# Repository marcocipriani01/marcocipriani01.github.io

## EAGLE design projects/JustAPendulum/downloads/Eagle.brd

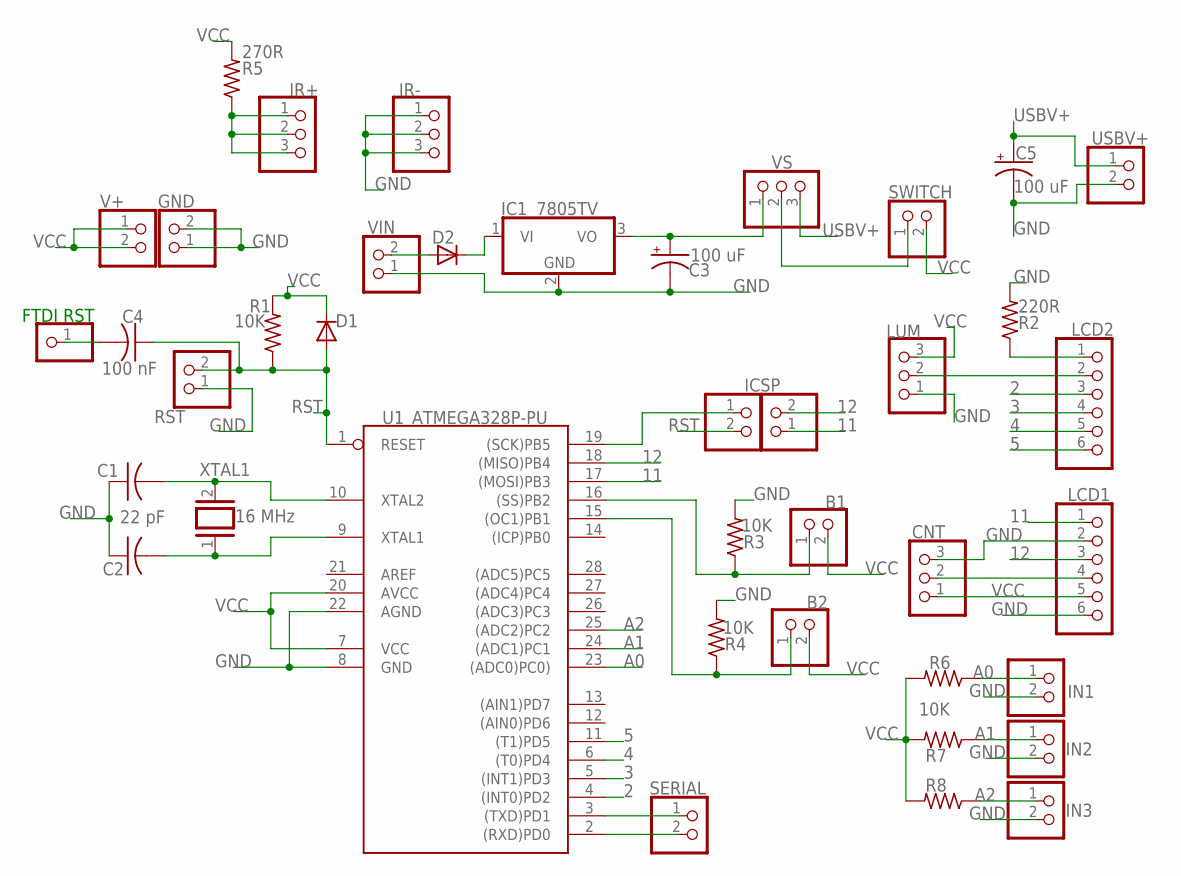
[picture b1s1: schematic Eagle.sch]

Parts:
B1, B2: PINHD-1X2; 1X02
C1, C2: 22 pF; C025-025X050
C3: 100 uF; E5-6
C4: 100 nF; C102-043X133
C5: 100 uF; B45181A
CNT: PINHD-1X3; 1X03
D1, D2: 1N4148DO35-7; DO35-7
FTDI_RST: PINHD-1X1; 1X01
GND: PINHD-1X2; 1X02
IC1: 7805TV; TO220V
ICSP, ICSP2: PINHD-1X2; 1X02
IN1, IN2, IN3: PINHD-1X2; 1X02
IR+: PINHD-1X3; 1X03
IR-: PINHD-1X3; 1X03
LCD1, LCD2: PINHD-1X6; 1X06
LUM: PINHD-1X3; 1X03
R1, R3, R4, R6, R7, R8: 10K; 0204/5
R2: 220R; 0204/5
R5: 270R; 0207/10
RST: PINHD-1X2; 1X02
SERIAL: PINHD-1X2; 1X02
SWITCH: PINHD-1X2; 1X02
U1: ATMEGA328P-PU; DIL28-3
USBV+: PINHD-1X2; 1X02
V+: PINHD-1X2; 1X02
VIN: PINHD-1X2; 1X02
VS: PINHD-1X3; 1X03
XTAL1: 16 MHz; QS

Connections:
2: LCD2.3, U1.4 ((INT0)PD2)
3: LCD2.4, U1.5 ((INT1)PD3)
4: LCD2.5, U1.6 ((T0)PD4)
5: LCD2.6, U1.11 ((T1)PD5)
10: B1.1, R3.1, U1.16 ((SS)PB2)
11: ICSP2.1, LCD1.1, U1.17 ((MOSI)PB3)
12: ICSP2.2, LCD1.3, U1.18 ((MISO)PB4)
A0: IN1.1, R6.1, U1.23 ((ADC0)PC0))
A1: IN2.1, R7.1, U1.24 ((ADC1)PC1)
A2: IN3.1, R8.1, U1.25 ((ADC2)PC2)
GND: C1.1, C2.1, C3.-, C5.-, CNT.3, GND.1, GND.2, IC1.2 (GND), IN1.2, IN2.2, IN3.2, IR-.1, IR-.2, IR-.3, LCD1.2, LCD1.6, LUM.1, R2.2, R3.2, R4.2, RST.1, U1.8 (GND), U1.22 (AGND), USBV+.2, VIN.1
unnamed: C3.+, IC1.3 (VO), VS.1
unnamed: C1.2, U1.10 (XTAL2), XTAL1.2
unnamed: C2.2, U1.9 (XTAL1), XTAL1.1
unnamed: D2.A, VIN.2
unnamed: D2.C, IC1.1 (VI)
unnamed: C4.2, FTDI_RST.1
unnamed: ICSP.1, U1.19 ((SCK)PB5)
unnamed: B2.1, R4.1, U1.15 ((OC1)PB1)
unnamed: SWITCH.1, VS.2
unnamed: LCD2.1, R2.1
unnamed: CNT.2, LCD1.4
unnamed: LCD2.2, LUM.2
unnamed: IR+.1, IR+.2, IR+.3, R5.1
RST: C4.1, D1.A, ICSP.2, R1.1, RST.2, U1.1 (RESET)
RX: SERIAL.2, U1.2 ((RXD)PD0)
TX: SERIAL.1, U1.3 ((TXD)PD1)
USBV+: C5.+, USBV+.1, VS.3
VCC: B1.2, B2.2, CNT.1, D1.C, LCD1.5, LUM.3, R1.2, R5.2, R6.2, R7.2, R8.2, SWITCH.2, U1.7 (VCC), U1.20 (AVCC), V+.1, V+.2

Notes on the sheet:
FTDI RST

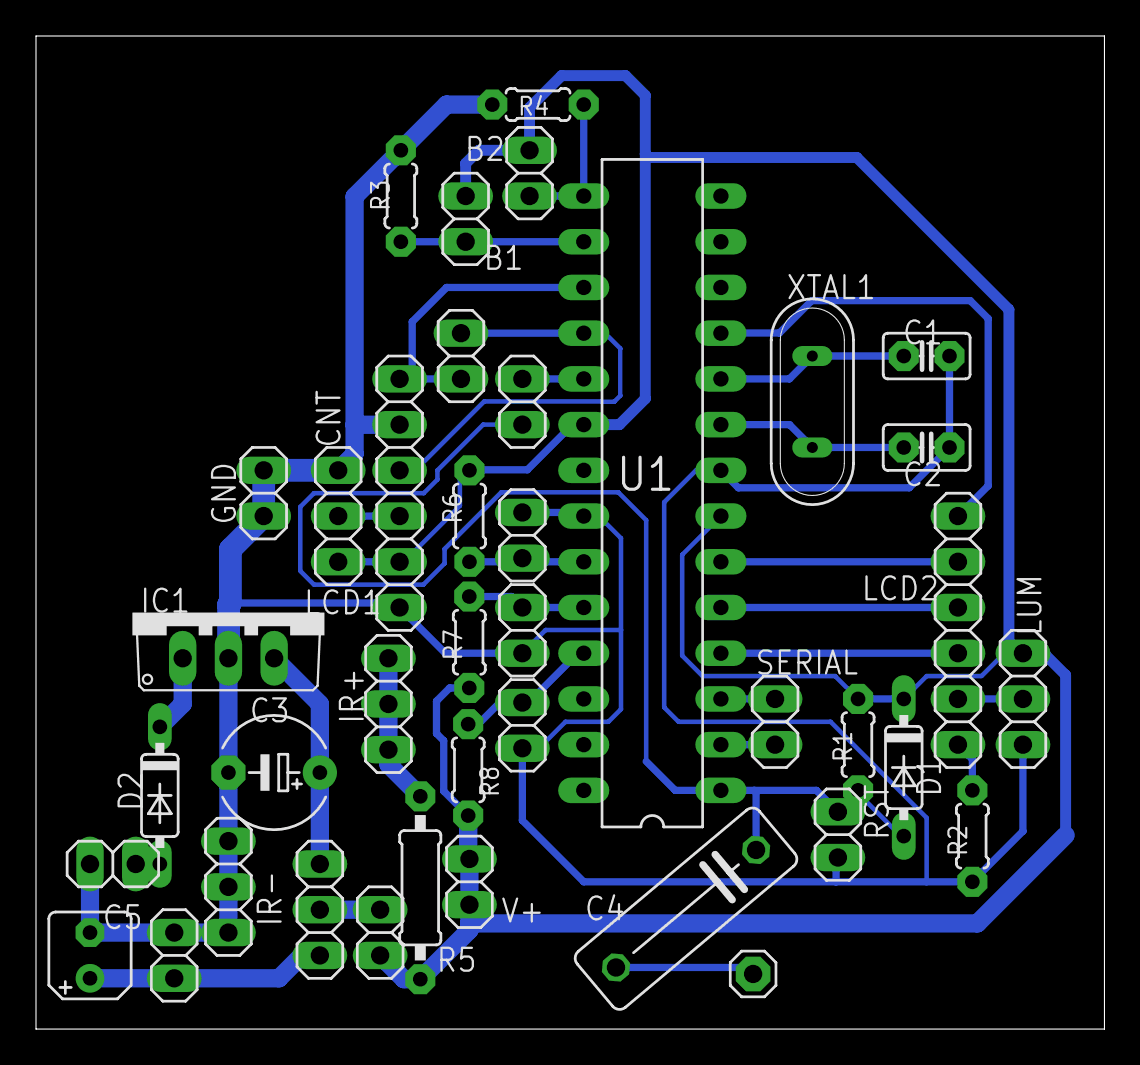
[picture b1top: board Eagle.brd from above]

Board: 2 copper layers, 59.4 x 55.2 mm, 40 parts (0 on the bottom side), 29 nets.

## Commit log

2019-08-22 Added files
2019-08-23 Added 2018 Star Party post, to be finished
2019-08-23 Added Dumbbell Nebula description
2019-08-24 Added Space Camp post
2019-08-24 Update ESC post
2020-04-24 Add shop
2020-04-24 Fix cookie consent
2020-04-24 Fix privacy
2020-04-24 Add message on index page
2020-04-24 Fix FB link
2020-12-22 Refresh
2020-12-24 Add Caprile Observatory
2021-01-21 Fix forms
2021-03-31 Auto Flat test
2021-03-31 Drivers
2021-04-29 Update Auto Flat

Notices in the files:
projects/JustAPendulum/downloads/Eagle.brd:
CC BY-NC-SA
